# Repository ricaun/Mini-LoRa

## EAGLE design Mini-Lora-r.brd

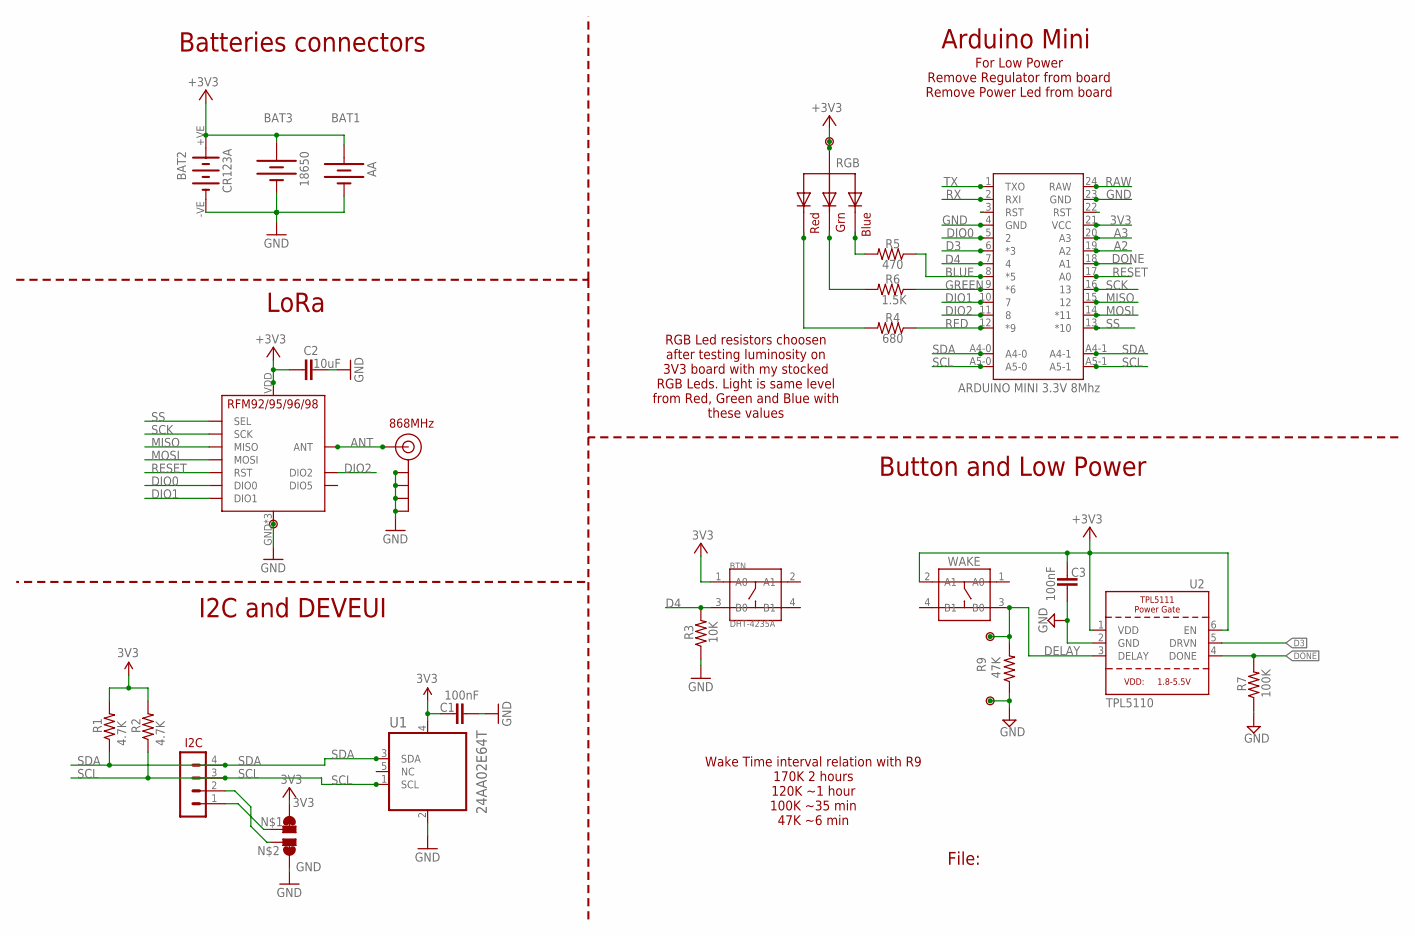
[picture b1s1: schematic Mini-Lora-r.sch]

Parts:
BAT1: AA; BATTERY-AA
BAT2: CR123A; KEYSTONE-2/3A
BAT3: 18650; BATTERY_18650-HOLDER
BTN: DHT-4235A; SW4-SMD-4.2X3.2X2.5MM
C1, C3: 100nF; 0805-CAP
C2: 10uF; 0805-CAP-LARGEPADS
I2C: CON_HEADER_1X04'NO_LOCK'; 1X04_NO_LOCK
J$2: ANTENNATINY; SMA_UFL_PAD_TINY
P1: GND; PAD
P2, P3, P4: PADNORMAL; PAD
R1, R2: 4.7K; 0805-RES
R3: 10K; 0805-RES
R4: 680; 0805-RES
R5: 470; 0805-RES
R6: 1.5K; 0805-RES
R7: 100K; 0805-RES
R9: 47K; 1206-RES
RGB: RGBLED; LED5MMRGB_ST
U1: 24AA02E64T; SOT95P270X145-5N
U2: TPL5110; SOT23-6
U$1: PAD-JUMPER-SWAPSWAP; PAD-JUMPER-SWAP
U$5: RFM95
U$6: ARDUINO MINI 3.3V 8Mhz; ARDUINO_PRO_MINI
WAKE: WAKE; SW4-SMD-4.2X3.2X2.5MM

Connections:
3V3: BAT1.PWR@1 (+), BAT2.+VE (+), BAT3.PWR@1 (+), BTN.1 (A0), C1.1, C2.2, C3.1, P4.1, R1.2, R2.2, RGB.2 (VCC), U1.4 (VCC), U2.1 (VDD), U2.6 (EN), U$1.4, U$1.44 (4), U$5.VDD (VCC), U$6.21 (VCC), WAKE.2 (A1)
A2: U$6.19 (A2)
A3: U$6.20 (A3)
ANT: J$2.ANT1 (SIGNAL), J$2.ANT2 (SIGNAL), J$2.ANT3 (SIGNAL), U$5.ANT
BLUE: R5.1, U$6.8 (*5)
D3: U2.5 (DRVN), U$6.6 (*3)
D4: BTN.3 (B0), R3.2, U$6.7 (4)
DELAY: P2.1, R9.2, U2.3 (DELAY), WAKE.3 (B0)
DIO0: U$5.DIO0, U$6.5 (2)
DIO1: U$5.DIO1, U$6.10 (7)
DIO2: U$5.DIO2, U$6.11 (8)
DONE: R7.2, U2.4 (DONE), U$6.18 (A1)
GND: BAT1.GND@1 (-), BAT2.-VE (-), BAT3.GND@1 (-), C1.2, C2.1, C3.2, J$2.GND1 (GND), J$2.GND2 (GND), J$2.GND3 (GND), J$2.GND4 (GND), P1.1, P3.1, R3.1, R7.1, R9.1, U1.2 (VSS), U2.2 (GND), U$1.1, U$1.11 (1), U$5.GND, U$5.GND1 (GND), U$5.GND2 (GND), U$6.4 (GND), U$6.23 (GND)
GREEN: R6.1, U$6.9 (*6)
LB: R5.2, RGB.4 (BLUE)
LG: R6.2, RGB.3 (GREEN)
LR: R4.2, RGB.1 (RED)
MISO: U$5.MISO, U$6.15 (12)
MOSI: U$5.MOSI, U$6.14 (*11)
unnamed: I2C.1, U$1.3
unnamed: I2C.2, U$1.2
RAW: U$6.24 (RAW)
RED: R4.1, U$6.12 (*9)
RESET: U$5.RST, U$6.17 (A0)
RST: U$6.22 (RST)
RX: U$6.2 (RXI)
SCK: U$5.SCK, U$6.16 (13)
SCL: I2C.3, R2.1, U1.1 (SCL), U$6.A5-0, U$6.A5-1
SDA: I2C.4, R1.1, U1.3 (SDA), U$6.A4-0, U$6.A4-1
SS: U$5.NSS (SEL), U$6.13 (*10)
TX: U$6.1 (TXO)

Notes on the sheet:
File:
868MHz
Wake Time interval relation with R9 170K 2 hours 120K ~1 hour 100K ~35 min 47K ~6 min
Button and Low Power
Arduino Mini
I2C and DEVEUI
LoRa
Batteries connectors
For Low Power Remove Regulator from board Remove Power Led from board
RGB Led resistors choosen after testing luminosity on 3V3 board with my stocked RGB Leds. Light is same level from Red, Green and Blue with these values

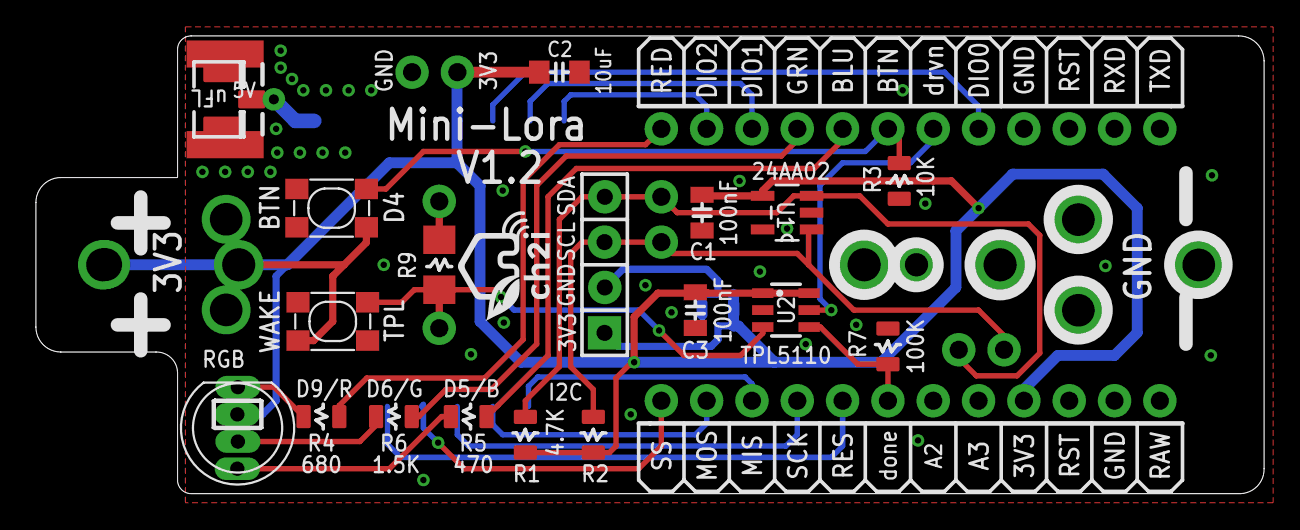
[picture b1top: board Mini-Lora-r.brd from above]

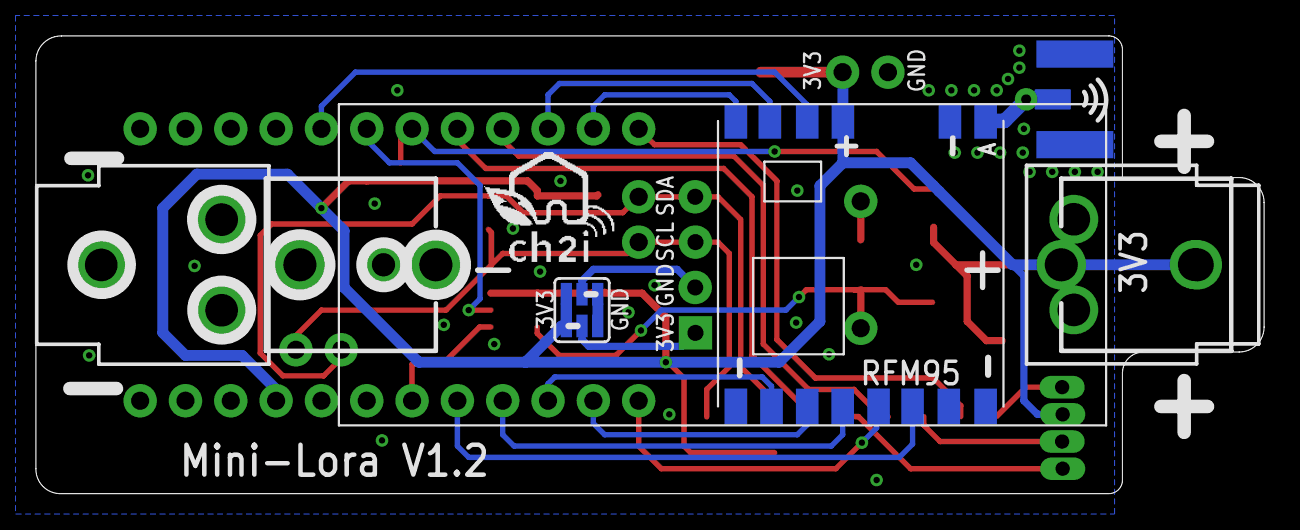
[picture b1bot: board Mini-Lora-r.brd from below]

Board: 2 copper layers, 68.8 x 25.7 mm, 30 parts (6 on the bottom side), 25 nets.

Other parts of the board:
U$2: LOGO_C2I_015
U$4: LOGO_CH2I_75MM

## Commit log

2018-08-13 Add my Version
    Change pin D3 to D4
    And Change A2 to D3

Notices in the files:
parts and their libraries:
edeca.net-v5: This is v1 and is licensed under the Creative Commons (Attribution-Non-Commercial-Share Alike 2.0 UK)
SparkFun-Aesthetics: Licensing: Creative Commons ShareAlike 4.0 International - https://creativecommons.org/licenses/by-sa/4.0
